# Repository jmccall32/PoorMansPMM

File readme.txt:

Rev A board with indicator LEDs added in place of reed relays and spare terminals

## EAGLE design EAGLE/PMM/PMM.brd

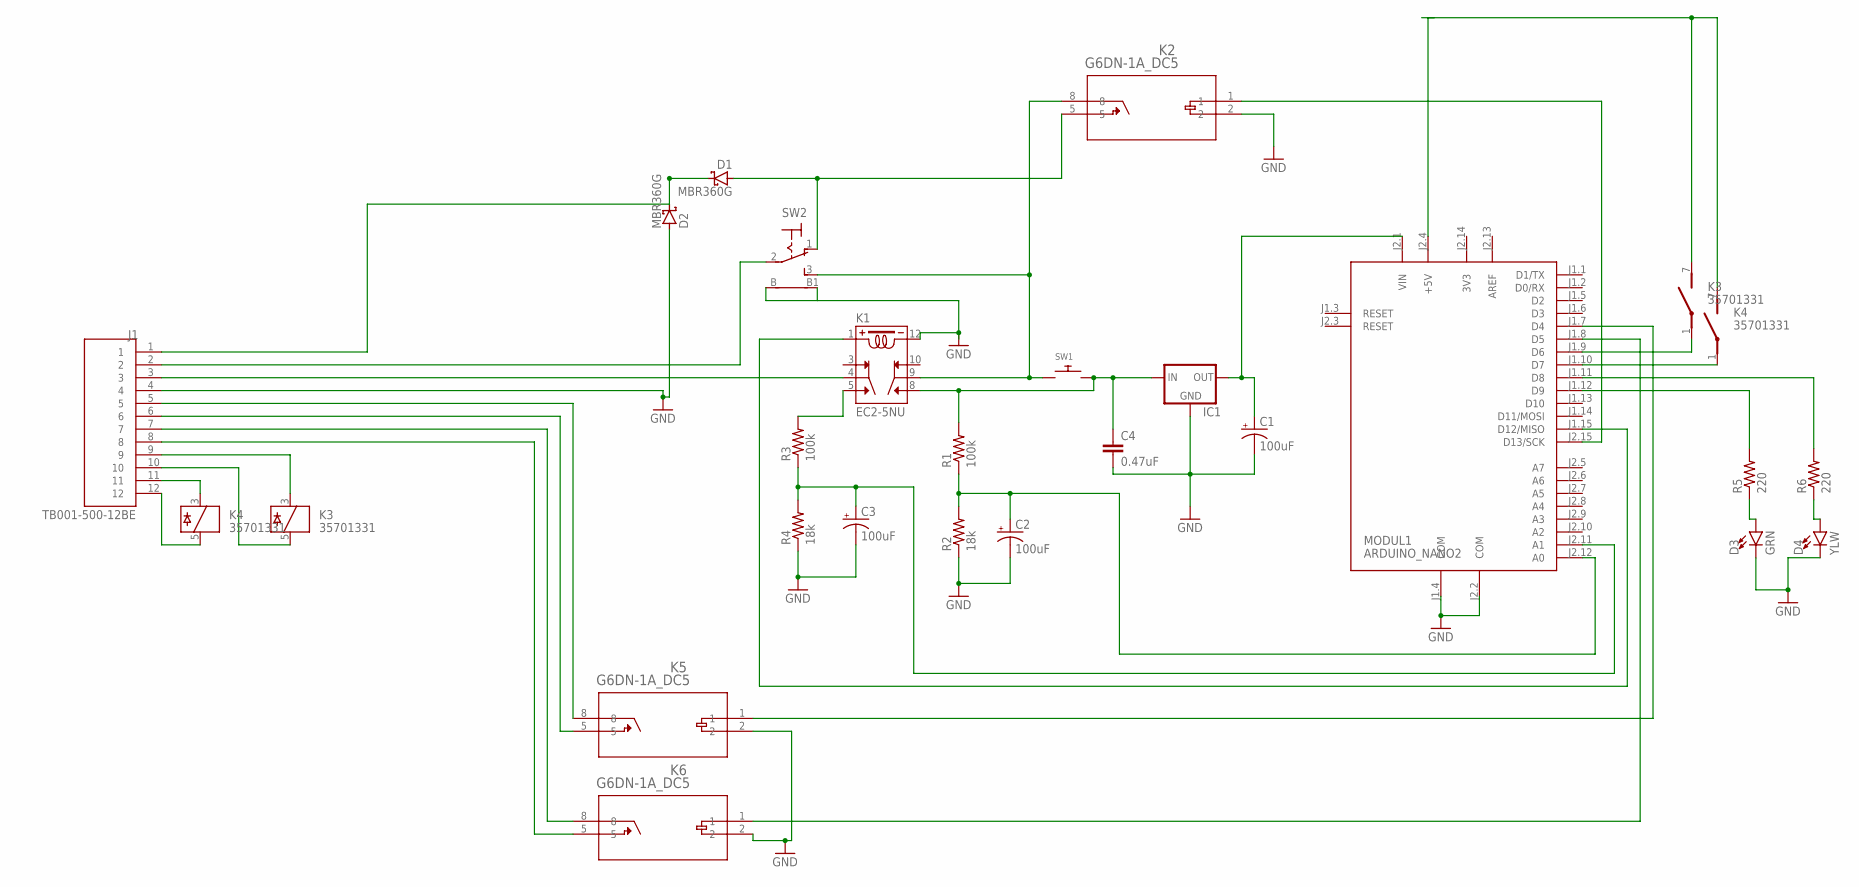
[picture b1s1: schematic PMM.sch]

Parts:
C1, C2, C3: 100uF; E2,5-7
C4: 0.47uF; C10B6
D1, D2: MBR360G; DO201AD
D3: GRN; LED_5MM-KIT
D4: YLW; LED_5MM-KIT
IC1: 78XXS
J1: TB001-500-12BE; CUI_TB001-500-12BE
K1: EC2-5NU; RELAY_EC2-5NU
K2, K5, K6: G6DN-1A_DC5; RELAY_G6DN-1A_OMR
K3, K4: 35701331; REED
MODUL1: ARDUINO_NANO2
R1, R3: 100k; 0207/12
R2, R4: 18k; 0207/12
R5, R6: 220; 0207/12
SW1: SWITCH_PUSHBUTTONON-MOM.2; TACT_PANA-EVQ
SW2: M20130M2013S2A2W30; M201*30

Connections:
3V3: MODUL1.J2.14 (3V3)
AREF: MODUL1.J2.13 (AREF)
GND: C1.-, C2.-, C3.-, C4.2, D2.A, D3.K (C), D4.K (C), IC1.GND, J1.4, K1.12, K2.2, K5.2, K6.2, MODUL1.J1.4 (COM), MODUL1.J2.2 (COM), R2.1, R4.1, SW2.B, SW2.B1
unnamed: J1.2, SW2.2
unnamed: D1.A, K2.5, SW2.1 (O)
unnamed: K1.9, K2.8, SW1.P$1, SW2.3 (S)
unnamed: C4.1, IC1.IN, K1.8, R1.2, SW1.P$2
unnamed: K2.1, MODUL1.J2.15 (D13/SCK)
unnamed: D4.A, R6.1
unnamed: J1.3, K1.4
unnamed: C2.+, MODUL1.J2.12 (A0), R1.1, R2.2
unnamed: D1.C, D2.C, J1.1
unnamed: C1.+, IC1.OUT, MODUL1.J2.1 (VIN)
unnamed: C3.+, MODUL1.J2.11 (A1), R3.1, R4.2
unnamed: K1.5, R3.2
unnamed: K3.7 (S), K4.7 (S), MODUL1.J2.4 (+5V)
unnamed: J1.9, K3.3
unnamed: J1.12, K4.5
unnamed: J1.10, K3.5
unnamed: K6.1, MODUL1.J1.8 (D5)
unnamed: K5.1, MODUL1.J1.7 (D4)
unnamed: K3.1, MODUL1.J1.9 (D6)
unnamed: J1.11, K4.3
unnamed: K4.1, MODUL1.J1.10 (D7)
unnamed: K1.1, MODUL1.J1.15 (D12/MISO)
unnamed: D3.A, R5.1
unnamed: MODUL1.J1.11 (D8), R6.2
unnamed: MODUL1.J1.12 (D9), R5.2
unnamed: J1.5, K5.8
unnamed: J1.6, K5.5
unnamed: J1.7, K6.8
unnamed: J1.8, K6.5

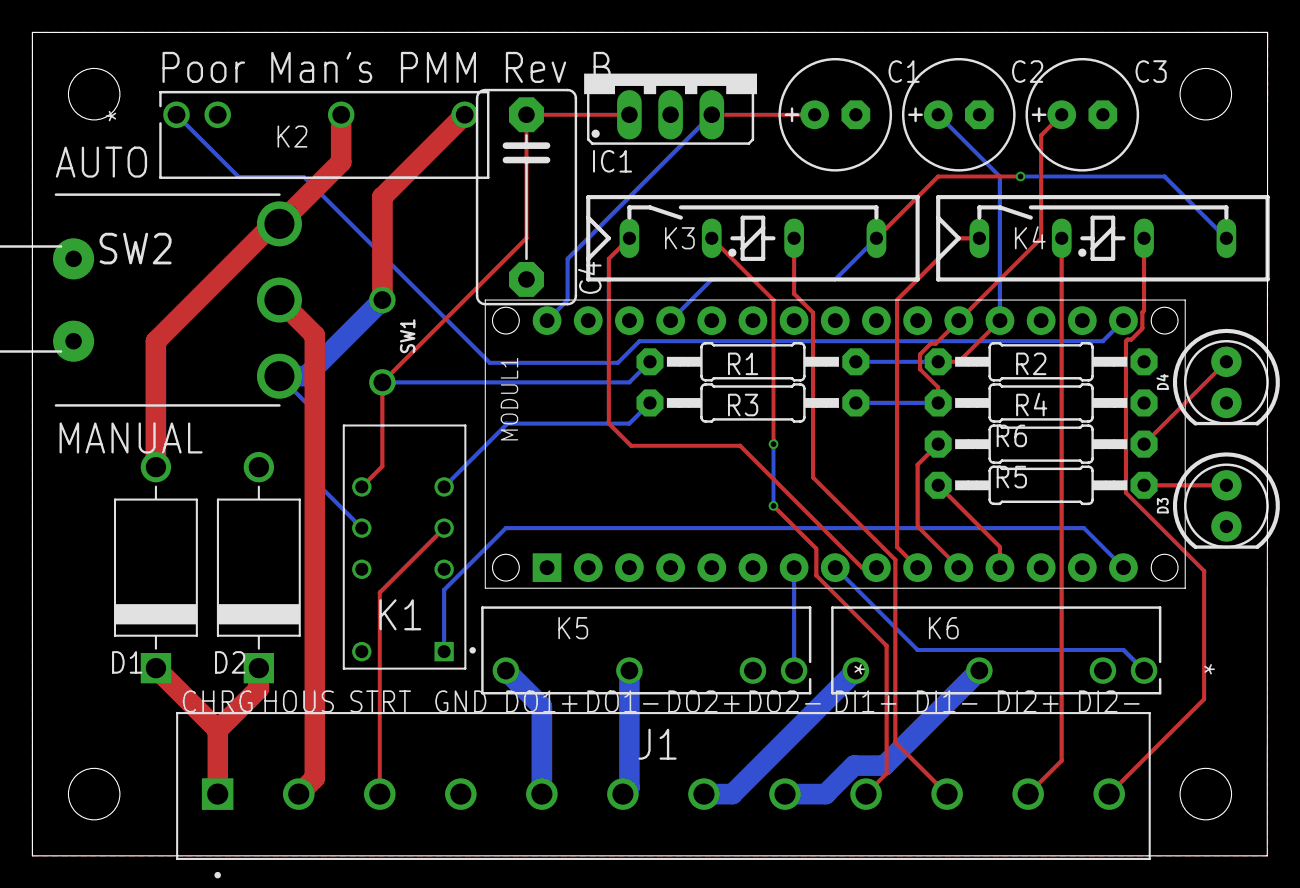
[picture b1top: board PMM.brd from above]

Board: 2 copper layers, 76.2 x 50.8 mm, 25 parts (0 on the bottom side), 30 nets.

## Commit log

2021-01-27 Added Eagle files
2021-01-27 Added eagle pcb & scr files
2021-01-27 Arduino IDE changed directory names
2021-01-28 Minor format fixes
2021-02-20 Changed digital out pins to match layout
2021-02-20 Typo in memory loading routine
2021-02-20 Correct analog pins
2021-02-20 Added startup delay
2021-02-22 Improved settings updating via serial
2021-02-22 Updated C4 value
2021-02-27 Added range checking for EEPROM loading and indicator LED outputs
2021-03-01 Showing mods for indicator LEDs, no spare I/O
2021-03-11 Switched D12 & D13 to have on-board indicator for on state
2021-03-11 Corrected SW2 footprint
2021-03-11 Added indicator LEDs
2021-03-11 Indicator LEDs moved to correct channels
2021-03-12 Rotated LEDs to bring pads in from board edge
2021-03-14 Changed spare DIO to 2 in, 2 out, all relay isolated
2021-08-26 Edited comments; no code changes
2022-02-25 Changed logic to prioritize cross-charging from house to start even when house is not actively being charged
2022-02-27 Just bug fixes
2022-02-27 Changed cross-charging logic to prioritize charging start battery from house battery, even when house battery is not being actively charged
2022-02-27 Minor bug fix
2022-02-28 Deployed to van 2/27/2022
2022-02-28 Added explicit "booting" state Deployed to van 2/28/2022
2022-03-02 Revert "First build"
2022-03-02 New boot logic
2022-03-02 Synced variable names with main
2022-03-02 Hopefully this creates a new "as-built" branch after the previous cluster. Variable naming reconciled with main.
2022-03-02 Added data logging mode
2022-03-03 Made differential voltage asymmetrical Deployed to van 3/2/22
2022-03-03 Moved booting state into main state machine Changed most ints to longs
2022-03-03 replaced functions "loadFloatSetpoint" and "loadUnsignedSetpoint" with overloaded functions "loadSetpoint"
2022-03-07 Added wait to stop cross-charging Deployed to van 3/7/22
2022-03-09 Updated status light behavior
2022-03-09 Made it an option to limit cross-charging to times when at least one battery is actively being charged
2022-03-11 Changed settings to reduce contactor cycling
2022-03-12 Updated to allow slower serial connection and make cycle time more nearly deterministic
2022-03-12 Padded state names to equal length to solve display bug in serial terminal Made exit from data logging mode happen on same loop cycle
2022-03-17 Even more deterministic timing
2022-03-17 Fixed weird times on first couple rows of Data Logging Mode output
2022-03-22 Minor formatting
2022-03-22 renamed "state" to "currentState"
2022-03-22 Turned state IDs into an enum
2022-03-22 Bumped baud rate up to 19200
2022-03-22 Minor improvements to cycle timing and status display
2022-03-22 Clear screen on startup
2022-03-22 Formatting & comments
2022-03-22 Extensive updates to plotSerialLog.m

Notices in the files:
parts and their libraries:
SparkFun-LED: Licensing: Creative Commons ShareAlike 4.0 International - https://creativecommons.org/licenses/by-sa/4.0
COPYRIGHT: Copyright (C) 2018 Accelerated Designs. All rights reserved
